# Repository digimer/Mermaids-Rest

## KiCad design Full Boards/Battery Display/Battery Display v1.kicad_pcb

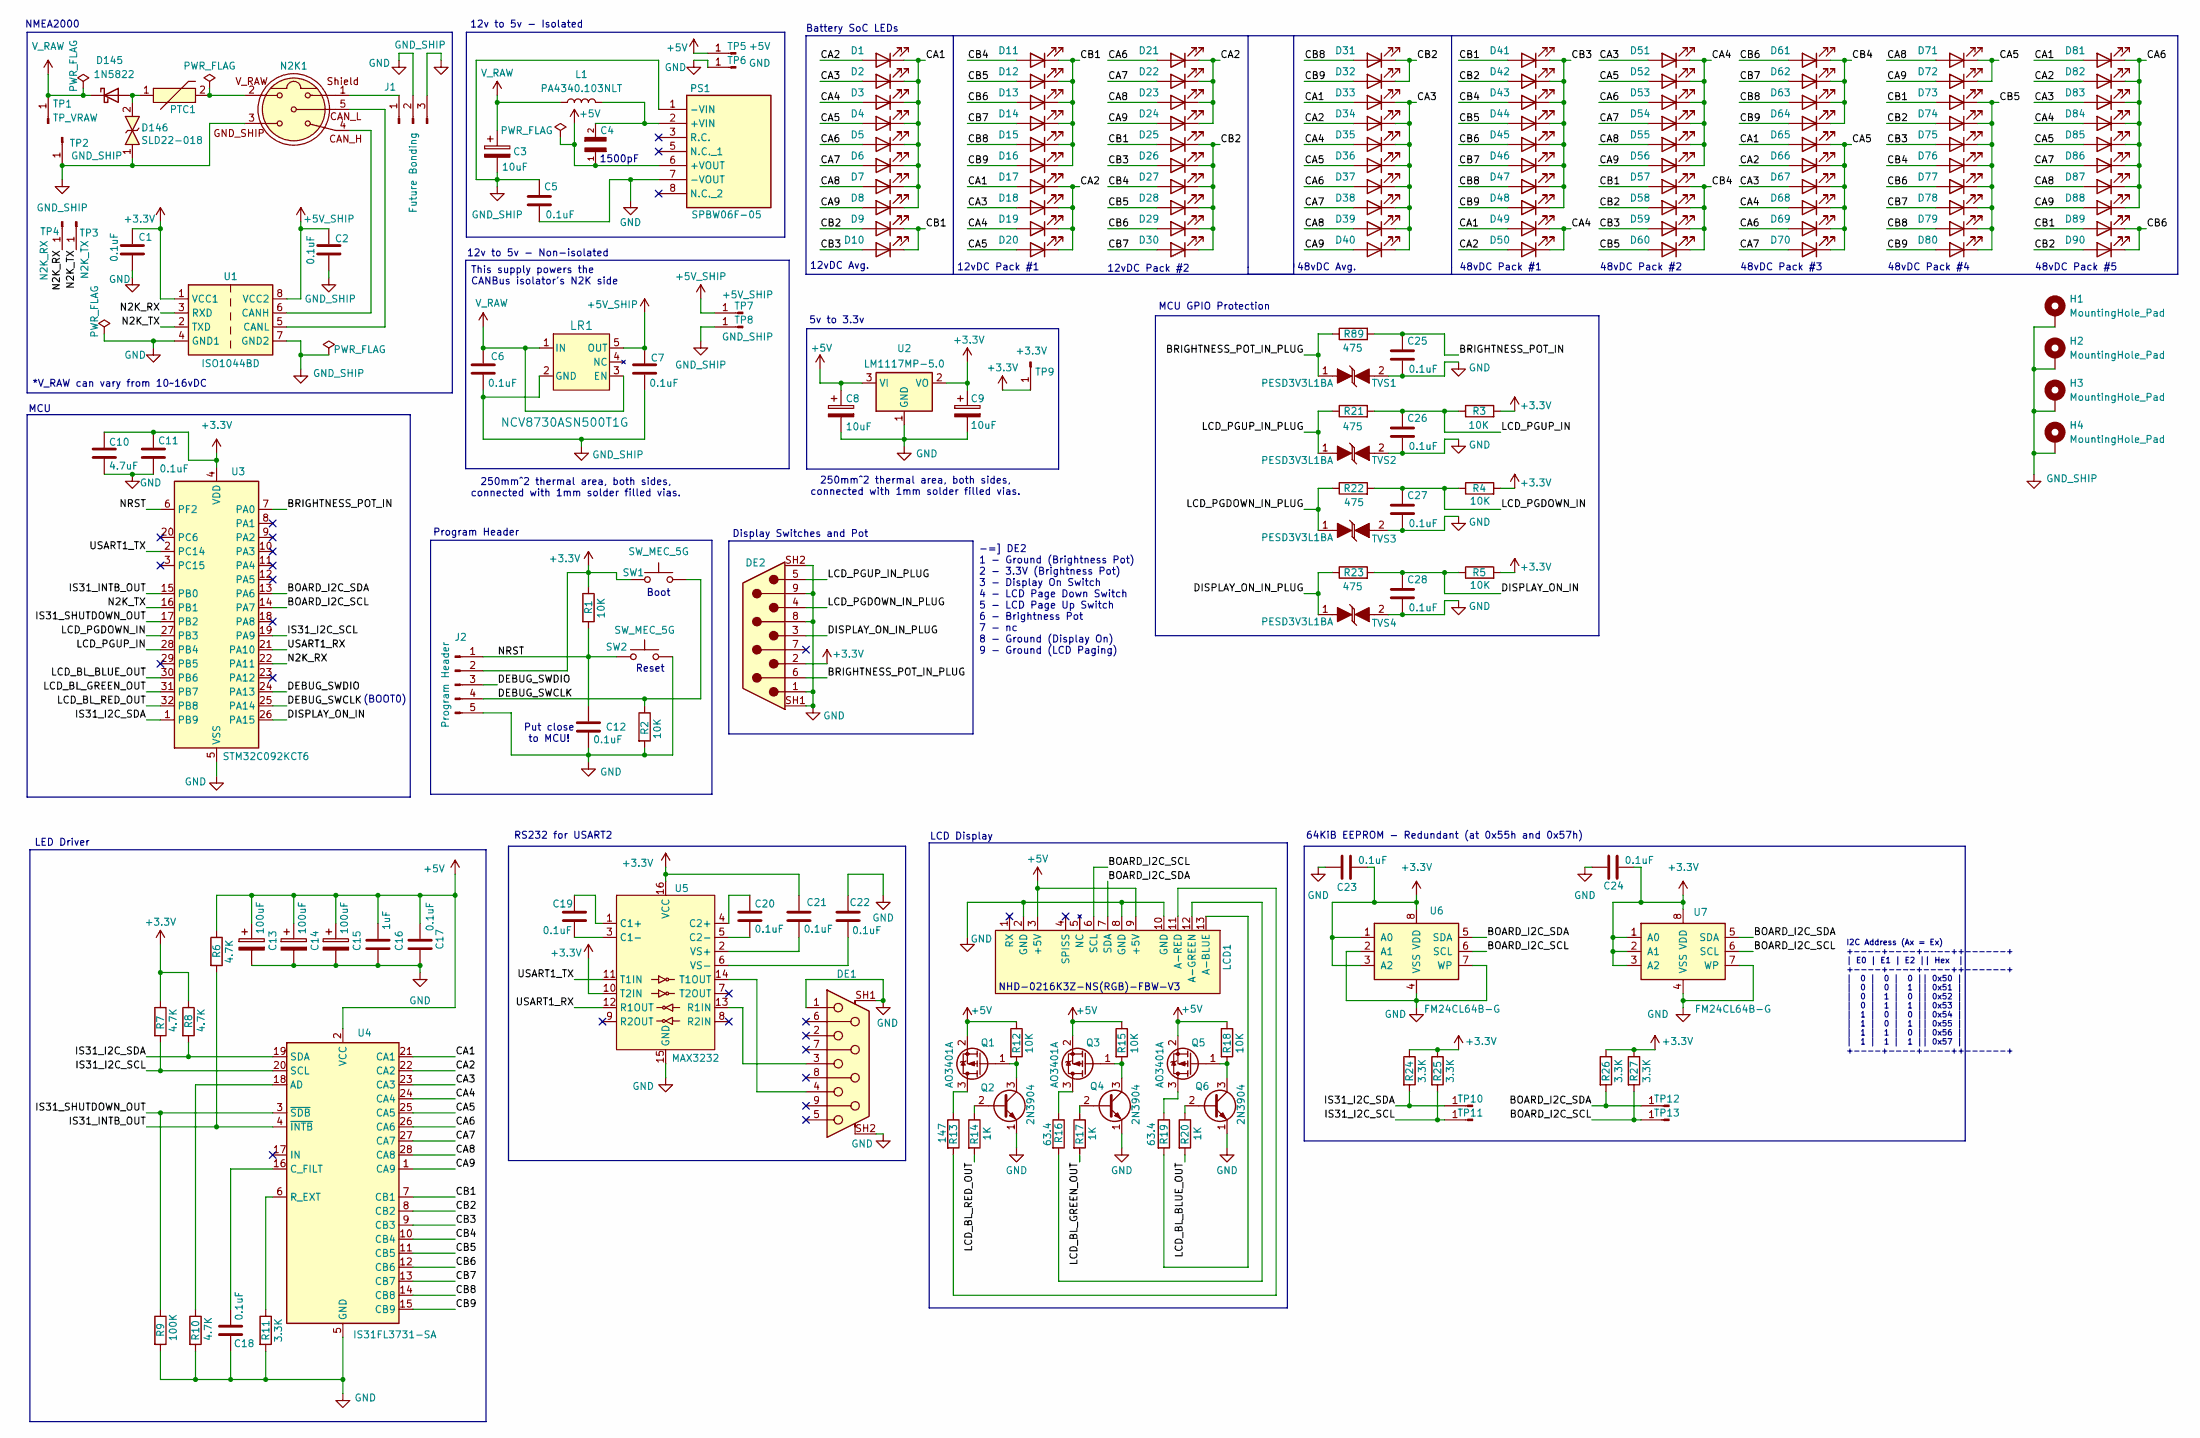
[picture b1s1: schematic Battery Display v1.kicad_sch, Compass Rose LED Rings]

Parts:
C1, C2, C5, C6, C7, C11, C12, C17, C18, C19, C20, C21, C22, C23, C24, C25, C26, C27, C28: 0.1uF; RCE5C1H104J2A2H03B
C3, C8, C9: 10uF; CP_Radial_D8.0mm_P3.50mm
C4: TDK FA28NP01H152JNU06; TDK CAPRB500W50L400T250H550; PARTREV 20200318
C10: 4.7uF; RCER71E475K2A2H03B
C13, C14, C15: 100uF; CP_Radial_D8.0mm_P5.00mm
C16: 1uF; C_Rect_L7.2mm_W7.2mm_P5.00mm_FKS2_FKP2_MKS2_MKP2
D1, D2, D3, D4, D5, D6, D7, D8, D9, D10, D11, D12, D13, D14, D15, D16, D17, D18, D19, D20, D21, D22, D23, D24, D25, D26, D27, D28, D29, D30, D31, D32, D33, D34, D35, D36, D37, D38, D39, D40, D41, D42, D43, D44, D45, D46, D47, D48, D49, D50, D51, D52, D53, D54, D55, D56, D57, D58, D59, D60, D61, D62, D63, D64, D65, D66, D67, D68, D69, D70, D71, D72, D73, D74, D75, D76, D77, D78, D79, D80, D81, D82, D83, D84, D85, D86, D87, D88, D89, D90: LED; WP383SURDTK
D145: 1N5822; D_DO-201AD_P15.24mm_Horizontal
D146: SLD22-018; DIOAD4425W136L885D885; Manufacturer_Part_Number SLD15-018; Mouser Part Number 576-SLD15-018
DE1: Amphenol_L77SDE09SA4CH4F
DE2: Amphenol_L777SDE09PA4CH4F
H1, H2, H3, H4: MountingHole_Pad; MountingHole_4mm_Pad_Via
J1: Future Bonding; PinHeader_1x03_P2.54mm_Horizontal
J2: Program Header; PinHeader_1x05_P2.54mm_Horizontal
L1: PA4340.103NLT; Pulse PA4340.103NLT
LCD1: NHD-0216K3Z-NS(RGB)-FBW-V3
LR1: NCV8730ASN500T1G; TSOP-5_483_OSI
N2K1: M12B-05PMMR
PS1: SPBW06F-05; SPBW06F05; Manufacturer_Part_Number SPBW06F-05; Mouser Part Number 709-SPBW06F-05
PTC1: PTC; AHEF100
Q1, Q3, Q5: AO3401A; SOT-23
Q2, Q4, Q6: 2N3904; TO-92_Inline
R1, R2, R3, R4, R5, R12, R15, R18: 10K; R_Axial_DIN0207_L6.3mm_D2.5mm_P7.62mm_Horizontal
R6, R7, R8, R10: 4.7K; R_Axial_DIN0207_L6.3mm_D2.5mm_P7.62mm_Horizontal
R9: 100K; R_Axial_DIN0207_L6.3mm_D2.5mm_P7.62mm_Horizontal
R11, R24, R25, R26, R27: 3.3K; R_Axial_DIN0207_L6.3mm_D2.5mm_P7.62mm_Horizontal
R13: 147; R_Axial_DIN0207_L6.3mm_D2.5mm_P7.62mm_Horizontal
R14, R17, R20: 1K; R_Axial_DIN0207_L6.3mm_D2.5mm_P7.62mm_Horizontal
R16, R19: 63.4; R_Axial_DIN0207_L6.3mm_D2.5mm_P7.62mm_Horizontal
R21, R22, R23, R89: 475; R_Axial_DIN0207_L6.3mm_D2.5mm_P7.62mm_Horizontal
SW1, SW2: SW_MEC_5G; SW_TS03-66-50-BK-160-LCR-D-67
TP1: TP_VRAW; PinHeader_1x01_P2.54mm_Vertical
TP2, TP8, TP11, TP13: GND_SHIP; PinHeader_1x01_P2.54mm_Vertical
TP3: N2K_TX; PinHeader_1x01_P2.54mm_Vertical
TP4: N2K_RX; PinHeader_1x01_P2.54mm_Vertical
TP5: +5V; PinHeader_1x01_P2.54mm_Vertical
TP6: GND; PinHeader_1x01_P2.54mm_Vertical
TP7, TP10, TP12: +5V_SHIP; PinHeader_1x01_P2.54mm_Vertical
TP9: +3.3V; PinHeader_1x01_P2.54mm_Vertical
TVS1, TVS2, TVS3, TVS4: PESD3V3L1BA; D_SOD-323
U1: ISO1044BD; SOIC-8_3.9x4.9mm_P1.27mm
U2: LM1117MP-5.0; SOT-223-3_TabPin2
U3: STM32C092KCT6; QFN-32-1EP_5x5mm_P0.5mm_EP3.45x3.45mm
U4: IS31FL3731-SA; SSOP-28_5.3x10.2mm_P0.65mm
U5: MAX3232; TSSOP-16_4.4x5mm_P0.65mm
U6, U7: FM24CL64B-G; SOIC-8_3.9x4.9mm_P1.27mm

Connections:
+3.3V: C1.1, C9.1, C10.1, C11.1, C21.1, C23.1, C24.1, DE2.2, J2.2, R1.1, R3.2, R4.2, R5.2, R7.1, R8.1, R24.1, R25.1, R26.1, R27.1, SW1.1 (A), SW1.2 (A), TP9.1, U1.1 (VCC1), U2.2 (VO), U3.4 (VDD), U5.10 (T2IN), U5.16 (VCC), U6.1 (A0), U6.3 (A2), U6.8 (VDD), U7.1 (A0), U7.2 (A1), U7.3 (A2), U7.8 (VDD)
+5V: C4.1, C8.1, C13.1, C14.1, C15.1, C16.1, C17.1, LCD1.3 (+5V), LCD1.9 (+5V), PS1.6 (+VOUT), Q1.2 (S), Q3.2 (S), Q5.2 (S), R6.1, R12.1, R15.1, R18.1, TP5.1, U2.3 (VI), U4.2 (VCC)
+5V_SHIP: C2.1, C7.1, LR1.5 (OUT), TP7.1, U1.8 (VCC2)
/BOARD_I2C_SCL: LCD1.6 (SCL), R27.2, TP13.1, U3.14 (PA7), U6.6 (SCL), U7.6 (SCL)
/BOARD_I2C_SDA: LCD1.7 (SDA), R26.2, TP12.1, U3.13 (PA6), U6.5 (SDA), U7.5 (SDA)
/BRIGHTNESS_POT_IN: C25.1, R89.2, U3.7 (PA0)
/BRIGHTNESS_POT_IN_PLUG: DE2.6, R89.1, TVS1.1
/CA1: D1.1 (K), D2.1 (K), D3.1 (K), D4.1 (K), D5.1 (K), D6.1 (K), D7.1 (K), D8.1 (K), D17.2 (A), D33.2 (A), D49.2 (A), D65.2 (A), D81.2 (A), U4.21 (CA1)
/CA2: D1.2 (A), D17.1 (K), D18.1 (K), D19.1 (K), D20.1 (K), D21.1 (K), D22.1 (K), D23.1 (K), D24.1 (K), D34.2 (A), D50.2 (A), D66.2 (A), D82.2 (A), U4.22 (CA2)
/CA3: D2.2 (A), D18.2 (A), D33.1 (K), D34.1 (K), D35.1 (K), D36.1 (K), D37.1 (K), D38.1 (K), D39.1 (K), D40.1 (K), D51.2 (A), D67.2 (A), D83.2 (A), U4.23 (CA3)
/CA4: D3.2 (A), D19.2 (A), D35.2 (A), D49.1 (K), D50.1 (K), D51.1 (K), D52.1 (K), D53.1 (K), D54.1 (K), D55.1 (K), D56.1 (K), D68.2 (A), D84.2 (A), U4.24 (CA4)
/CA5: D4.2 (A), D20.2 (A), D36.2 (A), D52.2 (A), D65.1 (K), D66.1 (K), D67.1 (K), D68.1 (K), D69.1 (K), D70.1 (K), D71.1 (K), D72.1 (K), D85.2 (A), U4.25 (CA5)
/CA6: D5.2 (A), D21.2 (A), D37.2 (A), D53.2 (A), D69.2 (A), D81.1 (K), D82.1 (K), D83.1 (K), D84.1 (K), D85.1 (K), D86.1 (K), D87.1 (K), D88.1 (K), U4.26 (CA6)
/CA7: D6.2 (A), D22.2 (A), D38.2 (A), D54.2 (A), D70.2 (A), D86.2 (A), U4.27 (CA7)
/CA8: D7.2 (A), D23.2 (A), D39.2 (A), D55.2 (A), D71.2 (A), D87.2 (A), U4.28 (CA8)
/CA9: D8.2 (A), D24.2 (A), D40.2 (A), D56.2 (A), D72.2 (A), D88.2 (A), U4.1 (CA9)
/CB1: D9.1 (K), D10.1 (K), D11.1 (K), D12.1 (K), D13.1 (K), D14.1 (K), D15.1 (K), D16.1 (K), D25.2 (A), D41.2 (A), D57.2 (A), D73.2 (A), D89.2 (A), U4.7 (CB1)
/CB2: D9.2 (A), D25.1 (K), D26.1 (K), D27.1 (K), D28.1 (K), D29.1 (K), D30.1 (K), D31.1 (K), D32.1 (K), D42.2 (A), D58.2 (A), D74.2 (A), D90.2 (A), U4.8 (CB2)
/CB3: D10.2 (A), D26.2 (A), D41.1 (K), D42.1 (K), D43.1 (K), D44.1 (K), D45.1 (K), D46.1 (K), D47.1 (K), D48.1 (K), D59.2 (A), D75.2 (A), U4.9 (CB3)
/CB4: D11.2 (A), D27.2 (A), D43.2 (A), D57.1 (K), D58.1 (K), D59.1 (K), D60.1 (K), D61.1 (K), D62.1 (K), D63.1 (K), D64.1 (K), D76.2 (A), U4.10 (CB4)
/CB5: D12.2 (A), D28.2 (A), D44.2 (A), D60.2 (A), D73.1 (K), D74.1 (K), D75.1 (K), D76.1 (K), D77.1 (K), D78.1 (K), D79.1 (K), D80.1 (K), U4.11 (CB5)
/CB6: D13.2 (A), D29.2 (A), D45.2 (A), D61.2 (A), D77.2 (A), D89.1 (K), D90.1 (K), U4.12 (CB6)
/CB7: D14.2 (A), D30.2 (A), D46.2 (A), D62.2 (A), D78.2 (A), U4.13 (CB7)
/CB8: D15.2 (A), D31.2 (A), D47.2 (A), D63.2 (A), D79.2 (A), U4.14 (CB8)
/CB9: D16.2 (A), D32.2 (A), D48.2 (A), D64.2 (A), D80.2 (A), U4.15 (CB9)
/DEBUG_SWCLK: J2.4, R2.1, SW1.3 (B), SW1.4 (B), U3.25 (PA14)
/DEBUG_SWDIO: J2.3, U3.24 (PA13)
/DISPLAY_ON_IN: C28.1, R5.1, R23.2, U3.26 (PA15)
/DISPLAY_ON_IN_PLUG: DE2.3, R23.1, TVS4.1
/IS31_I2C_SCL: R7.2, R25.2, TP11.1, U3.19 (PA9), U4.20 (SCL)
/IS31_I2C_SDA: R8.2, R24.2, TP10.1, U3.1 (PB9), U4.19 (SDA)
/IS31_INTB_OUT: R6.2, U3.15 (PB0), U4.4 (~INTB)
/IS31_SHUTDOWN_OUT: R9.1, U3.17 (PB2), U4.3 (~SDB)
/LCD_BL_BLUE_OUT: R20.2, U3.30 (PB6)
/LCD_BL_GREEN_OUT: R17.2, U3.31 (PB7)
/LCD_BL_RED_OUT: R14.2, U3.32 (PB8)
/LCD_PGDOWN_IN: C27.1, R4.1, R22.2, U3.27 (PB3)
/LCD_PGDOWN_IN_PLUG: DE2.4, R22.1, TVS3.1
/LCD_PGUP_IN: C26.1, R3.1, R21.2, U3.28 (PB4)
/LCD_PGUP_IN_PLUG: DE2.5, R21.1, TVS2.1
/N2K_RX: TP4.1, U1.3 (RXD), U3.22 (PA11)
/N2K_TX: TP3.1, U1.2 (TXD), U3.16 (PB1)
/NRST: C12.1, J2.1, R1.2, SW2.1 (A), SW2.2 (A), U3.6 (PF2)
/USART1_RX: U3.21 (PA10), U5.12 (R1OUT)
/USART1_TX: U3.2 (PC14), U5.11 (T1IN)
GND: C1.2, C5.2, C8.2, C9.2, C10.2, C11.2, C12.2, C13.2, C14.2, C15.2, C16.2, C17.2, C18.2, C22.2, C23.2, C24.2, C25.2, C26.2, C27.2, C28.2, DE1.1, DE1.SH1, DE1.SH2, DE2.1, DE2.8, DE2.9, DE2.SH1, DE2.SH2, J1.2, J2.5, LCD1.2 (GND), LCD1.8 (GND), LCD1.10 (GND), PS1.7 (-VOUT), Q2.1 (E), Q4.1 (E), Q6.1 (E), R2.2, R9.2, R10.2, R11.2, SW2.3 (B), SW2.4 (B), TP6.1, TVS1.2, TVS2.2, TVS3.2, TVS4.2, U1.4 (GND1), U2.1 (GND), U3.5 (VSS), U3.33 (VSS), U4.5 (GND), U5.15 (GND), U6.2 (A1), U6.4 (VSS), U6.7 (WP), U7.4 (VSS), U7.7 (WP)
GND_SHIP: C2.2, C3.2, C5.1, C6.2, C7.2, D146.1, H1.1, H2.1, H3.1, H4.1, J1.3, LR1.2 (GND), N2K1.3, PS1.1 (-VIN), TP2.1, TP8.1, U1.7 (GND2)
unnamed: D145.2 (A), D146.2, PTC1.1
unnamed: J1.1, N2K1.1
unnamed: LCD1.13 (A-BLUE), R19.2
unnamed: LCD1.12 (A-GREEN), R16.2
unnamed: LCD1.11 (A-RED), R13.2
unnamed: N2K1.2, PTC1.2
unnamed: C4.2, L1.2, PS1.2 (+VIN)
unnamed: Q1.3 (D), R13.1
unnamed: Q1.1 (G), Q2.3 (C), R12.2
unnamed: Q2.2 (B), R14.1
unnamed: Q3.3 (D), R16.1
unnamed: Q3.1 (G), Q4.3 (C), R15.2
unnamed: Q4.2 (B), R17.1
unnamed: Q5.3 (D), R19.1
unnamed: Q5.1 (G), Q6.3 (C), R18.2
unnamed: Q6.2 (B), R20.1
unnamed: N2K1.4, U1.6 (CANH)
unnamed: N2K1.5, U1.5 (CANL)
unnamed: R10.1, U4.18 (AD)
unnamed: C18.1, U4.16 (C_FILT)
unnamed: R11.1, U4.6 (R_EXT)
unnamed: C19.1, U5.1 (C1+)
unnamed: C19.2, U5.3 (C1-)
unnamed: C20.1, U5.4 (C2+)
unnamed: C20.2, U5.5 (C2-)
unnamed: DE1.3, U5.13 (R1IN)
unnamed: DE1.4, U5.14 (T1OUT)
unnamed: C21.2, U5.2 (VS+)
unnamed: C22.1, U5.6 (VS-)
V_RAW: C3.1, C6.1, D145.1 (K), L1.1, LR1.1 (IN), LR1.3 (EN), TP1.1

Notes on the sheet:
Battery SoC LEDs
250mm^2 thermal area, both sides, connected with 1mm solder filled vias.
12v to 5v - Non-isolated
48vDC Pack #2
48vDC Pack #3
48vDC Pack #4
Display Switches and Pot
12v to 5v - Isolated
MCU
48vDC Avg.
(BOOT0)
5v to 3.3v
LCD Display
-=] DE2 1 - Ground (Brightness Pot) 2 - 3.3V (Brightness Pot) 3 - Display On Switch 4 - LCD Page Down Switch 5 - LCD Page Up Switch 6 - Brightness Pot 7 - nc 8 - Ground (Display On) 9 - Ground (LCD Paging)
64KiB EEPROM - Redundant (at 0x55h and 0x57h)
MCU GPIO Protection
NHD-0216K3Z-NS(RGB)-FBW-V3
12vDC Pack #1
RS232 for USART2
1500pF
12vDC Pack #2
This supply powers the CANBus isolator's N2K side
Put close to MCU!
12vDC Avg.
I2C Address (Ax = Ex) +----+----+----++------+ | E0 | E1 | E2 || Hex | +----+----+----++------+ | 0 | 0 | 0 || 0x50 | | 0 | 0 | 1 || 0x51 | | 0 | 1 | 0 || 0x52 | | 0 | 1 | 1 || 0x53 | | 1 | 0 | 0 || 0x54 | | 1 | 0 | 1 || 0x55 | | 1 | 1 | 0 || 0x56 | | 1 | 1 | 1 || 0x57 | +----+----+----++------+
Program Header
Reset
*V_RAW can vary from 10~16vDC
48vDC Pack #5
LED Driver
Boot
NMEA2000
48vDC Pack #1

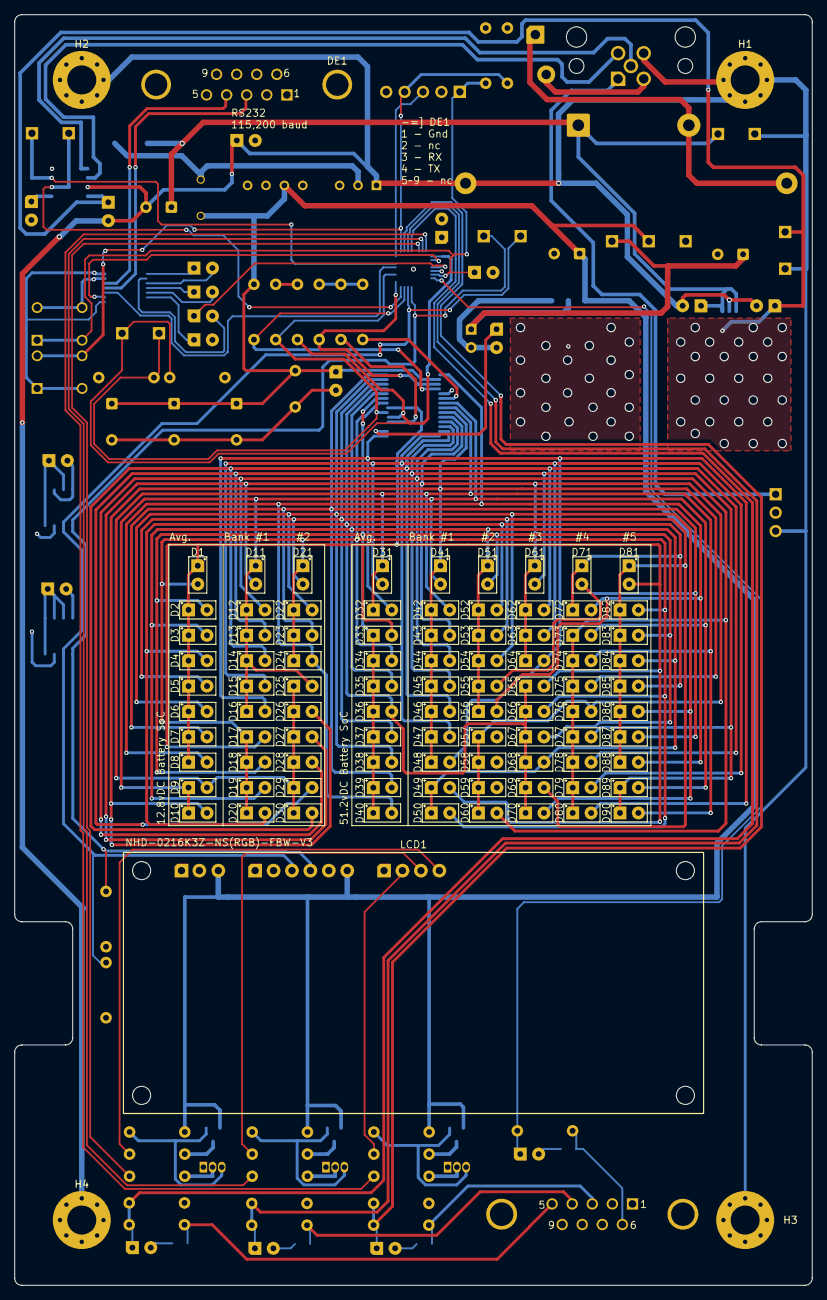
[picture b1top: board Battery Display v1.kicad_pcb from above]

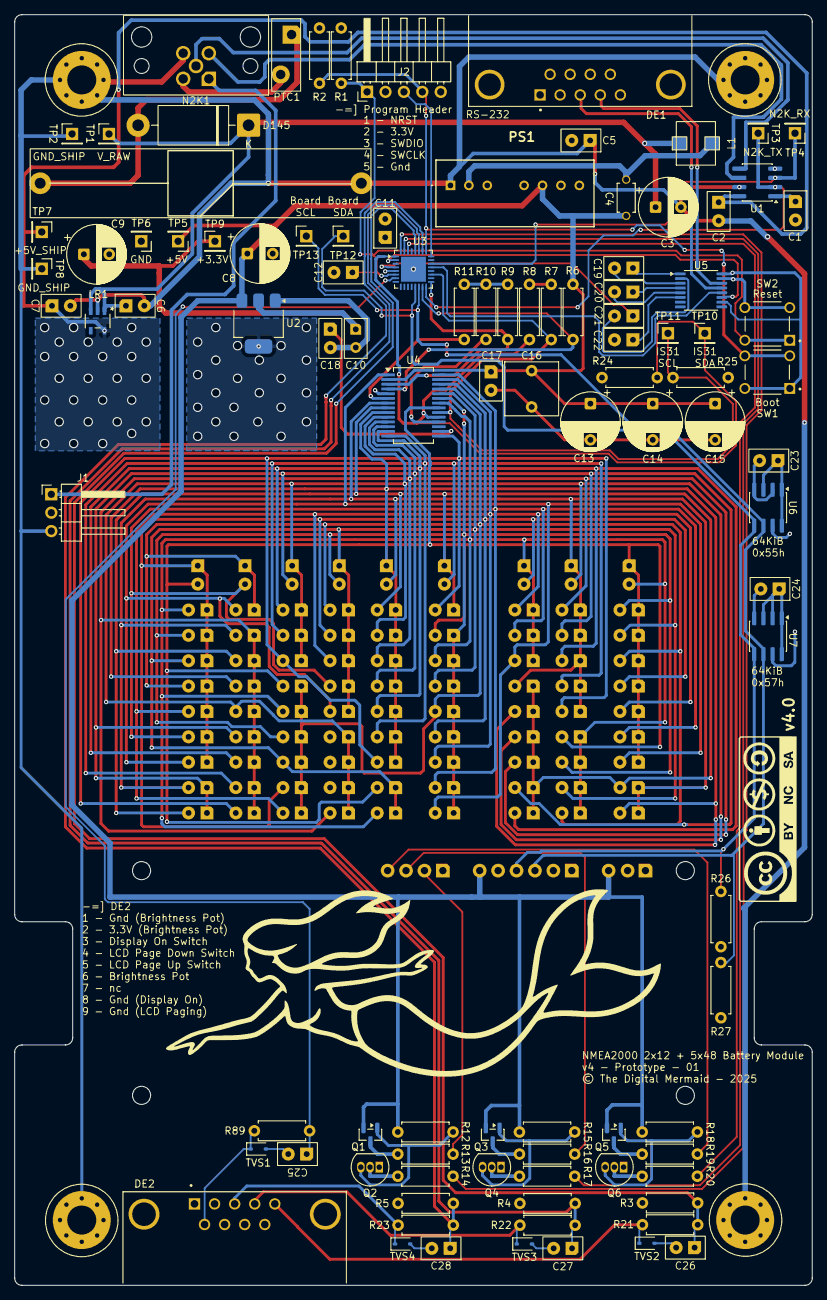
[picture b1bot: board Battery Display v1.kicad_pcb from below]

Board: 4 copper layers, 110.0 x 175.2 mm, 195 parts (100 on the bottom side), 77 nets.

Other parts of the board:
TDM***: LOGO; Mermaid Silkscreen - 29.9mm

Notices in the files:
Full Boards/Battery Display/Battery Display v1.kicad_pcb:
© The Digital Mermaid - 2025
Full Boards/Compass Rose/Compass Rose.kicad_pcb:
© The Digital Mermaid - 2026
CERN Open Hardware Licence
